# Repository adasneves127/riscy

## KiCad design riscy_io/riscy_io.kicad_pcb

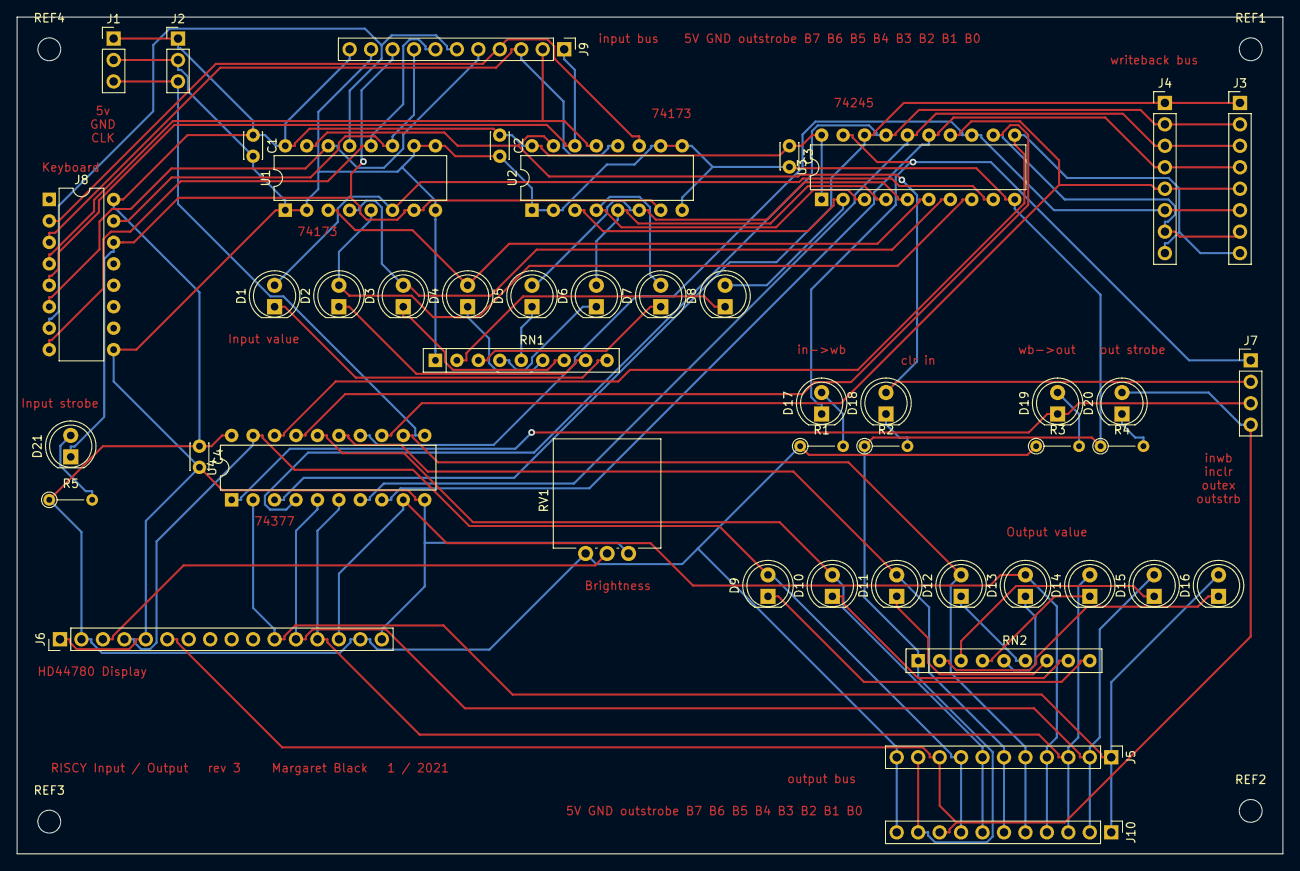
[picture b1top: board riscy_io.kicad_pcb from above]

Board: 2 copper layers, 149.9 x 99.1 mm, 51 parts (0 on the bottom side), 62 nets.

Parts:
C1, C2, C3, C4: C; C_Disc_D3.0mm_W2.0mm_P2.50mm
D1, D2, D3, D4, D5, D6, D7, D8, D9, D10, D11, D12, D13, D14, D15, D16, D17, D18, D19, D20, D21: LED; LED_D5.0mm
J1, J2: Conn_01x03_Female; PinHeader_1x03_P2.54mm_Vertical
J3, J4: Conn_01x08_Female; PinHeader_1x08_P2.54mm_Vertical
J5, J9, J10: Conn_01x11_Female; PinHeader_1x11_P2.54mm_Vertical
J6: Conn_01x16_Female; PinHeader_1x16_P2.54mm_Vertical
J7: Conn_01x04_Female; PinHeader_1x04_P2.54mm_Vertical
J8: Conn_01x16_Female; DIP-16_W7.62mm
R1, R2, R3, R4, R5: R; R_Axial_DIN0204_L3.6mm_D1.6mm_P5.08mm_Vertical
REF1, REF2, REF3, REF4: MountingHole_2.7mm_M2.5
RN1, RN2: R_Network08; R_Array_SIP9
RV1: R_POT; Potentiometer_Vishay_248GJ-249GJ_Single_Vertical
U1, U2: 74LS173; DIP-16_W7.62mm
U3: 74LS245; DIP-20_W7.62mm
U4: 74LS377; DIP-20_W7.62mm

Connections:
+5V: C1.1, C2.1, C3.1, C4.1, J1.1, J2.1, J5.11, J6.2, J6.15, J8.16, J9.11, J10.11, R1.1, R3.1, R5.1, RV1.3, U1.16, U2.16, U3.1, U3.20, U4.20
CLK: J1.3, J2.3, U4.11
GND: C1.2, C2.2, C3.2, C4.2, J1.2, J2.2, J5.10, J6.1, J6.5, J6.16, J8.9, J9.10, J10.10, R2.1, R4.1, RN1.1, RN2.1, RV1.1, U1.1, U1.2, U1.8, U1.9, U1.10, U2.1, U2.2, U2.8, U2.9, U2.10, U3.10, U4.10
unnamed: D1.1, RN1.9
unnamed: D1.2, U1.6, U3.9
unnamed: D2.1, RN1.8
unnamed: D2.2, U1.5, U3.8
unnamed: D3.1, RN1.7
unnamed: D3.2, U1.4, U3.7
unnamed: D4.1, RN1.6
unnamed: D4.2, U1.3, U3.6
unnamed: D5.1, RN1.5
unnamed: D5.2, U2.6, U3.5
unnamed: D6.1, RN1.4
unnamed: D6.2, U2.5, U3.4
unnamed: D7.1, RN1.3
unnamed: D7.2, U2.4, U3.3
unnamed: D8.1, RN1.2
unnamed: D8.2, U2.3, U3.2
unnamed: D9.1, RN2.9
unnamed: D9.2, J5.8, J6.4, J10.8, U4.19
unnamed: D10.1, RN2.8
unnamed: D10.2, J5.7, J10.7, U4.16
unnamed: D11.1, RN2.7
unnamed: D11.2, J5.6, J10.6, U4.15
unnamed: D12.1, RN2.6
unnamed: D12.2, J5.5, J10.5, U4.12
unnamed: D13.1, RN2.5
unnamed: D13.2, J5.4, J6.14, J10.4, U4.9
unnamed: D14.1, RN2.4
unnamed: D14.2, J5.3, J6.13, J10.3, U4.6
unnamed: D15.1, RN2.3
unnamed: D15.2, J5.2, J6.12, J10.2, U4.5
unnamed: D16.1, RN2.2
unnamed: D16.2, J5.1, J6.11, J10.1, U4.2
unnamed: D17.2, R1.2
unnamed: D18.1, R2.2
unnamed: D19.2, R3.2
unnamed: D20.1, R4.2
unnamed: D21.1, J8.14, J9.9, U1.7, U2.7
unnamed: D21.2, R5.2
unnamed: J3.1, J4.1, U3.18, U4.3
unnamed: J3.2, J4.2, U3.17, U4.4
unnamed: J3.3, J4.3, U3.16, U4.7
unnamed: J3.4, J4.4, U3.15, U4.8
unnamed: J3.5, J4.5, U3.14, U4.13
unnamed: J3.6, J4.6, U3.13, U4.14
unnamed: J3.7, J4.7, U3.12, U4.17
unnamed: J3.8, J4.8, U3.11, U4.18
unnamed: J6.3, RV1.2
unnamed: J8.2, J9.4, U2.11
unnamed: J8.3, J9.3, U2.12
unnamed: J8.4, J9.2, U2.13
unnamed: J8.5, J9.1, U2.14
unnamed: J8.6, J9.5, U1.14
unnamed: J8.7, J9.6, U1.13
unnamed: J8.8, J9.7, U1.12
unnamed: J8.15, J9.8, U1.11
inclr: D18.2, J7.2, U1.15, U2.15
inwb: D17.1, J7.1, U3.19
out3: D20.2, J5.9, J6.6, J7.4, J10.9
outex: D19.1, J7.3, U4.1

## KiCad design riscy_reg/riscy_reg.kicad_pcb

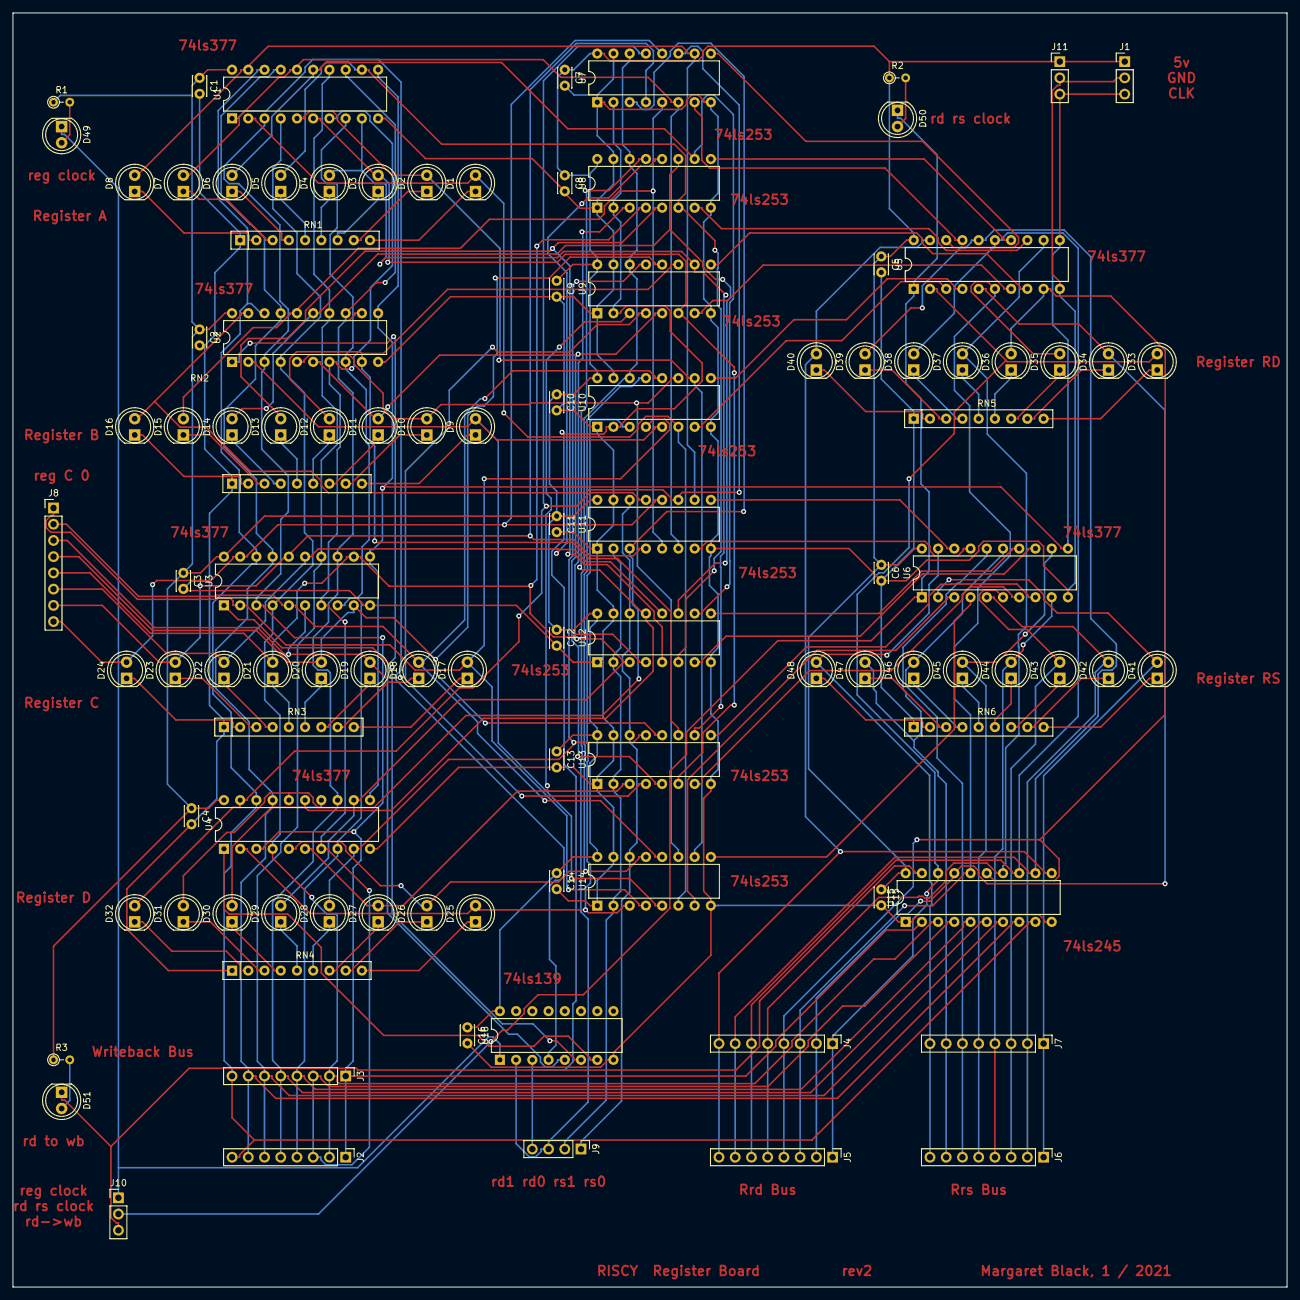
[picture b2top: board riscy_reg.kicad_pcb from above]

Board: 2 copper layers, 199.4 x 199.4 mm, 103 parts (0 on the bottom side), 137 nets.

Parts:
C1, C2, C3, C4, C5, C6, C7, C8, C9, C10, C11, C12, C13, C14, C15, C16: C; C_Disc_D3.0mm_W2.0mm_P2.50mm
D1, D2, D3, D4, D5, D6, D7, D8, D9, D10, D11, D12, D13, D14, D15, D16, D17, D18, D19, D20, D21, D22, D23, D24, D25, D26, D27, D28, D29, D30, D31, D32, D33, D34, D35, D36, D37, D38, D39, D40, D41, D42, D43, D44, D45, D46, D47, D48, D49, D50, D51: LED; LED_D5.0mm
J1, J10, J11: Conn_01x03_Female; PinHeader_1x03_P2.54mm_Vertical
J2, J3, J4, J5, J6, J7, J8: Conn_01x08_Female; PinHeader_1x08_P2.54mm_Vertical
J9: Conn_01x04_Female; PinHeader_1x04_P2.54mm_Vertical
R1, R2, R3: R; R_Axial_DIN0204_L3.6mm_D1.6mm_P2.54mm_Vertical
RN1, RN2, RN3, RN4, RN5, RN6: R_Network08; R_Array_SIP9
U1, U2, U3, U4, U5, U6: 74LS377; DIP-20_W7.62mm
U7, U8, U9, U10, U11, U12, U13, U14: 74LS253; DIP-16_W7.62mm
U15: 74LS245; DIP-20_W7.62mm
U16: 74LS139; DIP-16_W7.62mm

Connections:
+5V: C1.1, C2.1, C3.1, C4.1, C5.1, C6.1, C7.1, C8.1, C9.1, C10.1, C11.1, C12.1, C13.1, C14.1, C15.1, C16.1, J1.1, J11.1, R1.1, R2.1, R3.1, U1.20, U2.20, U3.20, U4.20, U5.20, U6.20, U7.16, U8.16, U9.16, U10.16, U11.16, U12.16, U13.16, U14.16, U15.20, U16.16
CLK: J1.3, J11.3, U1.11, U2.11, U3.11, U4.11, U5.11, U6.11
GND: C1.2, C2.2, C3.2, C4.2, C5.2, C6.2, C7.2, C8.2, C9.2, C10.2, C11.2, C12.2, C13.2, C14.2, C15.2, C16.2, J1.2, J11.2, RN1.1, RN2.1, RN3.1, RN4.1, RN5.1, RN6.1, U1.10, U2.10, U3.10, U4.10, U5.10, U6.10, U7.1, U7.8, U7.15, U8.1, U8.8, U8.15, U9.1, U9.8, U9.15, U10.1, U10.8, U10.15, U11.1, U11.8, U11.15, U12.1, U12.8, U12.15, U13.1, U13.8, U13.15, U14.1, U14.8, U14.15, U15.1, U15.10, U16.8
unnamed: D1.1, RN1.9
unnamed: D1.2, U1.2, U10.6, U14.6
unnamed: D2.1, RN1.8
unnamed: D2.2, U1.5, U10.10, U14.10
unnamed: D3.1, RN1.7
unnamed: D3.2, U1.6, U9.6, U13.6
unnamed: D4.1, RN1.6
unnamed: D4.2, U1.9, U9.10, U13.10
unnamed: D5.1, RN1.5
unnamed: D5.2, U1.12, U8.6, U12.6
unnamed: D6.1, RN1.4
unnamed: D6.2, U1.15, U8.10, U12.10
unnamed: D7.1, RN1.3
unnamed: D7.2, U1.16, U7.6, U11.6
unnamed: D8.1, RN1.2
unnamed: D8.2, U1.19, U7.10, U11.10
unnamed: D9.1, RN2.9
unnamed: D9.2, U2.2, U10.5, U14.5
unnamed: D10.1, RN2.8
unnamed: D10.2, U2.5, U10.11, U14.11
unnamed: D11.1, RN2.7
unnamed: D11.2, U2.6, U9.5, U13.5
unnamed: D12.1, RN2.6
unnamed: D12.2, U2.9, U9.11, U13.11
unnamed: D13.1, RN2.5
unnamed: D13.2, U2.12, U8.5, U12.5
unnamed: D14.1, RN2.4
unnamed: D14.2, U2.15, U8.11, U12.11
unnamed: D15.1, RN2.3
unnamed: D15.2, U2.16, U7.5, U11.5
unnamed: D16.1, RN2.2
unnamed: D16.2, U2.19, U7.11, U11.11
unnamed: D17.1, RN3.9
unnamed: D18.1, RN3.8
unnamed: D19.1, RN3.7
unnamed: D20.1, RN3.6
unnamed: D21.1, RN3.5
unnamed: D22.1, RN3.4
unnamed: D23.1, RN3.3
unnamed: D24.1, RN3.2
unnamed: D25.1, RN4.9
unnamed: D25.2, U4.2, U10.3, U14.3
unnamed: D26.1, RN4.8
unnamed: D26.2, U4.5, U10.13, U14.13
unnamed: D27.1, RN4.7
unnamed: D27.2, U4.6, U9.3, U13.3
unnamed: D28.1, RN4.6
unnamed: D28.2, U4.9, U9.13, U13.13
unnamed: D29.1, RN4.5
unnamed: D29.2, U4.12, U8.3, U12.3
unnamed: D30.1, RN4.4
unnamed: D30.2, U4.15, U8.13, U12.13
unnamed: D31.1, RN4.3
unnamed: D31.2, U4.16, U7.3, U11.3
unnamed: D32.1, RN4.2
unnamed: D32.2, U4.19, U7.13, U11.13
unnamed: D33.1, RN5.9
unnamed: D34.1, RN5.8
unnamed: D35.1, RN5.7
unnamed: D36.1, RN5.6
unnamed: D37.1, RN5.5
unnamed: D38.1, RN5.4
unnamed: D39.1, RN5.3
unnamed: D40.1, RN5.2
unnamed: D41.1, RN6.9
unnamed: D42.1, RN6.8
unnamed: D43.1, RN6.7
unnamed: D44.1, RN6.6
unnamed: D45.1, RN6.5
unnamed: D46.1, RN6.4
unnamed: D47.1, RN6.3
unnamed: D48.1, RN6.2
unnamed: D49.2, R1.2
unnamed: D50.2, R2.2
unnamed: D51.2, R3.2
unnamed: U1.1, U16.4
unnamed: U5.7, U9.7
unnamed: U5.8, U9.9
unnamed: U5.13, U8.7
unnamed: U5.14, U8.9
unnamed: U5.17, U7.7
unnamed: U5.18, U7.9
unnamed: U5.3, U10.7
unnamed: U5.4, U10.9
unnamed: U6.17, U11.7
unnamed: U6.18, U11.9
unnamed: U6.13, U12.7
unnamed: U6.14, U12.9
unnamed: U6.7, U13.7
unnamed: U6.8, U13.9
unnamed: U6.3, U14.7
unnamed: U6.4, U14.9
unnamed: U2.1, U16.5
unnamed: U3.1, U16.6
unnamed: U4.1, U16.7
Rrd0: D33.2, J4.1, J5.1, U5.2, U15.18
Rrd1: D34.2, J4.2, J5.2, U5.5, U15.17
Rrd2: D35.2, J4.3, J5.3, U5.6, U15.16
Rrd3: D36.2, J4.4, J5.4, U5.9, U15.15
Rrd4: D37.2, J4.5, J5.5, U5.12, U15.14
Rrd5: D38.2, J4.6, J5.6, U5.15, U15.13
Rrd6: D39.2, J4.7, J5.7, U5.16, U15.12
Rrd7: D40.2, J4.8, J5.8, U5.19, U15.11
Rrs0: D41.2, J6.1, J7.1, U6.2
Rrs1: D42.2, J6.2, J7.2, U6.5
Rrs2: D43.2, J6.3, J7.3, U6.6
Rrs3: D44.2, J6.4, J7.4, U6.9
Rrs4: D45.2, J6.5, J7.5, U6.12
Rrs5: D46.2, J6.6, J7.6, U6.15
Rrs6: D47.2, J6.7, J7.7, U6.16
Rrs7: D48.2, J6.8, J7.8, U6.19
c0: D17.2, J8.1, U3.2, U10.4, U14.4
c1: D18.2, J8.2, U3.5, U10.12, U14.12
c2: D19.2, J8.3, U3.6, U9.4, U13.4
c3: D20.2, J8.4, U3.9, U9.12, U13.12
c4: D21.2, J8.5, U3.12, U8.4, U12.4
c5: D22.2, J8.6, U3.15, U8.12, U12.12
c6: D23.2, J8.7, U3.16, U7.4, U11.4
c7: D24.2, J8.8, U3.19, U7.12, U11.12
rd0: J9.3, U7.14, U8.14, U9.14, U10.14, U16.2
rd1: J9.4, U7.2, U8.2, U9.2, U10.2, U16.3
rdrsclk: D50.1, J10.2, U5.1, U6.1
rdwb: D51.1, J10.3, U15.19
regclk: D49.1, J10.1, U16.1
rs0: J9.1, U11.14, U12.14, U13.14, U14.14
rs1: J9.2, U11.2, U12.2, U13.2, U14.2
wb0: J2.1, J3.1, U1.3, U2.3, U3.3, U4.3, U15.2
wb1: J2.2, J3.2, U1.4, U2.4, U3.4, U4.4, U15.3
wb2: J2.3, J3.3, U1.7, U2.7, U3.7, U4.7, U15.4
wb3: J2.4, J3.4, U1.8, U2.8, U3.8, U4.8, U15.5
wb4: J2.5, J3.5, U1.13, U2.13, U3.13, U4.13, U15.6
wb5: J2.6, J3.6, U1.14, U2.14, U3.14, U4.14, U15.7
wb6: J2.7, J3.7, U1.17, U2.17, U3.17, U4.17, U15.8
wb7: J2.8, J3.8, U1.18, U2.18, U3.18, U4.18, U15.9

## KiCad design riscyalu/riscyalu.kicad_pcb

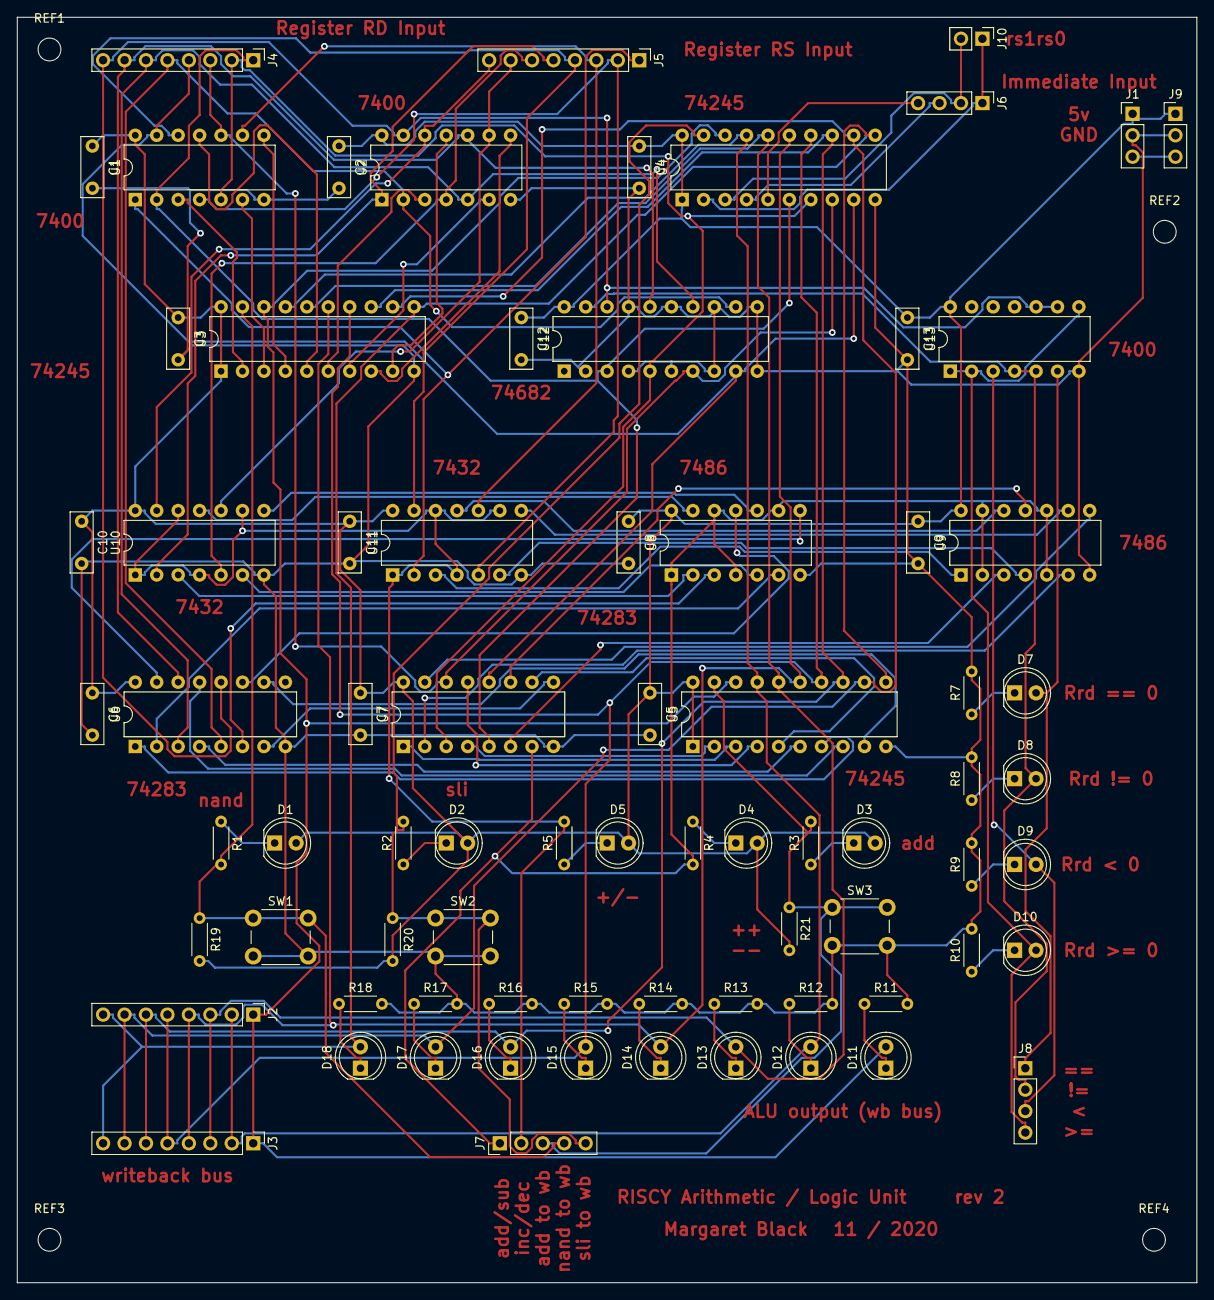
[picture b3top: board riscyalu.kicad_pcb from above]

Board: 2 copper layers, 139.7 x 149.9 mm, 80 parts (0 on the bottom side), 90 nets.

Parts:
C1, C2, C3, C4, C5, C6, C7, C8, C9, C10, C11, C12, C13: C; C_Disc_D7.0mm_W2.5mm_P5.00mm
D1, D2, D3, D4, D5, D7, D8, D9, D10, D11, D12, D13, D14, D15, D16, D17, D18: LED; LED_D5.0mm
J1, J9: Conn_01x03_Female; PinHeader_1x03_P2.54mm_Vertical
J2, J3, J4, J5: Conn_01x08_Female; PinHeader_1x08_P2.54mm_Vertical
J6, J8: Conn_01x04_Female; PinHeader_1x04_P2.54mm_Vertical
J7: Conn_01x05_Female; PinHeader_1x05_P2.54mm_Vertical
J10: Conn_01x02_Female; PinHeader_1x02_P2.54mm_Vertical
R1, R2, R3, R4, R5, R7, R8, R9, R10, R11, R12, R13, R14, R15, R16, R17, R18, R19, R20, R21: R; R_Axial_DIN0204_L3.6mm_D1.6mm_P5.08mm_Horizontal
REF1, REF2, REF3, REF4: MountingHole_2.7mm_M2.5
SW1, SW2, SW3: SW_Push; SW_PUSH_6mm_H4.3mm
U1, U2, U13: 7400; DIP-14_W7.62mm
U3, U4, U5: 74LS245; DIP-20_W7.62mm
U6, U7: 74LS283; DIP-16_W7.62mm
U8, U9: 74LS86; DIP-14_W7.62mm
U10, U11: 74LS32; DIP-14_W7.62mm
U12: 74LS682; DIP-20_W7.62mm

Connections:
+5V: C1.1, C2.1, C3.1, C4.1, C5.1, C6.1, C7.1, C8.1, C9.1, C10.1, C11.1, C12.1, C13.1, D1.2, D2.2, D3.2, D4.2, D5.2, J1.1, J9.1, R19.2, R20.2, R21.2, U1.14, U2.14, U3.1, U3.20, U4.1, U4.20, U5.1, U5.20, U6.16, U7.16, U8.14, U9.14, U10.14, U11.14, U12.20, U13.14
GND: C1.2, C2.2, C3.2, C4.2, C5.2, C6.2, C7.2, C8.2, C9.2, C10.2, C11.2, C12.2, C13.2, J1.2, J9.2, R7.2, R8.2, R9.2, R10.2, R11.2, R12.2, R13.2, R14.2, R15.2, R16.2, R17.2, R18.2, SW1.2, SW2.2, SW3.2, U1.7, U2.7, U3.10, U4.10, U5.10, U6.8, U7.8, U8.7, U9.7, U10.7, U11.7, U12.2, U12.4, U12.6, U12.8, U12.10, U12.11, U12.13, U12.15, U12.17, U13.7
unnamed: D1.1, R1.1
unnamed: D2.1, R2.1
unnamed: D3.1, R3.1
unnamed: D4.1, R4.1
unnamed: D5.1, R5.1
unnamed: D7.1, R7.1
unnamed: D8.1, R8.1
unnamed: D9.1, R9.1
unnamed: D10.1, R10.1
unnamed: D11.1, R11.1
unnamed: D12.1, R12.1
unnamed: D13.1, R13.1
unnamed: D14.1, R14.1
unnamed: D15.1, R15.1
unnamed: D16.1, R16.1
unnamed: D17.1, R17.1
unnamed: D18.1, R18.1
unnamed: J1.3, J9.3
unnamed: U1.3, U3.2
unnamed: U1.6, U3.3
unnamed: U1.8, U3.4
unnamed: U1.11, U3.5
unnamed: U2.3, U3.6
unnamed: U2.6, U3.7
unnamed: U2.8, U3.8
unnamed: U2.11, U3.9
unnamed: U5.2, U7.4
unnamed: U5.3, U7.1
unnamed: U5.4, U7.13
unnamed: U5.5, U7.10
unnamed: U5.6, U6.4
unnamed: U5.7, U6.1
unnamed: U5.8, U6.13
unnamed: U5.9, U6.10
unnamed: U6.2, U8.6
unnamed: U6.6, U8.3
unnamed: U6.7, U7.9
unnamed: U6.11, U8.11
unnamed: U6.15, U8.8
unnamed: U7.2, U9.6
unnamed: U7.6, U9.3
unnamed: U7.11, U9.11
unnamed: U7.15, U9.8
unnamed: U8.2, U10.3
unnamed: U8.5, U10.6
unnamed: U8.10, U10.8
unnamed: U8.13, U10.11
unnamed: U9.1, U11.3
unnamed: U9.4, U11.6
unnamed: U9.9, U11.8
unnamed: U9.12, U11.11
Rrd0: J4.1, U1.2, U4.6, U7.5, U12.3
Rrd1: J4.2, U1.5, U4.7, U7.3, U12.5
Rrd2: J4.3, U1.10, U4.8, U7.14, U12.7
Rrd3: J4.4, U1.13, U4.9, U7.12, U12.9
Rrd4: J4.5, U2.2, U6.5, U12.12
Rrd5: J4.6, U2.5, U6.3, U12.14
Rrd6: J4.7, U2.10, U6.14, U12.16
Rrd7: J4.8, U2.13, U6.12, U12.18, U13.9, U13.10
Rrs0: J5.1, U1.1, U11.2
Rrs1: J5.2, U1.4, U11.5
Rrs2: J5.3, U1.9, U11.10
Rrs3: J5.4, U1.12, U11.13
Rrs4: J5.5, U2.1, U10.2
Rrs5: J5.6, U2.4, U10.5
Rrs6: J5.7, U2.9, U10.10
Rrs7: J5.8, U2.12, U10.13
addsub: J7.1, R4.2, U7.7, U8.1, U8.4, U8.9, U8.12, U9.2, U9.5, U9.10, U9.13
addwb: J7.3, R3.2, R21.1, SW3.1, U5.19
eq: D7.2, J8.1, U13.6
ge: D10.2, J8.4, U13.1, U13.2, U13.8
imm0: J6.1, J10.1, U4.2
imm1: J6.2, J10.2, U4.3
imm2: J6.3, U4.4
imm3: J6.4, U4.5
incdec: J7.2, R5.2, U10.1, U10.4, U10.9, U10.12, U11.1, U11.4, U11.9, U11.12
lt: D9.2, J8.3, U13.3
nandwb: J7.4, R1.2, R19.1, SW1.1, U3.19
noteq: D8.2, J8.2, U12.19, U13.4, U13.5
sliwb: J7.5, R2.2, R20.1, SW2.1, U4.19
wb0: D11.2, J2.1, J3.1, U3.18, U4.18, U5.18
wb1: D12.2, J2.2, J3.2, U3.17, U4.17, U5.17
wb2: D13.2, J2.3, J3.3, U3.16, U4.16, U5.16
wb3: D14.2, J2.4, J3.4, U3.15, U4.15, U5.15
wb4: D15.2, J2.5, J3.5, U3.14, U4.14, U5.14
wb5: D16.2, J2.6, J3.6, U3.13, U4.13, U5.13
wb6: D17.2, J2.7, J3.7, U3.12, U4.12, U5.12
wb7: D18.2, J2.8, J3.8, U3.11, U4.11, U5.11
